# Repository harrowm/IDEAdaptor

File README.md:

# IDEAdaptor
A simple passive 40 to 44 pin ide adaptor board

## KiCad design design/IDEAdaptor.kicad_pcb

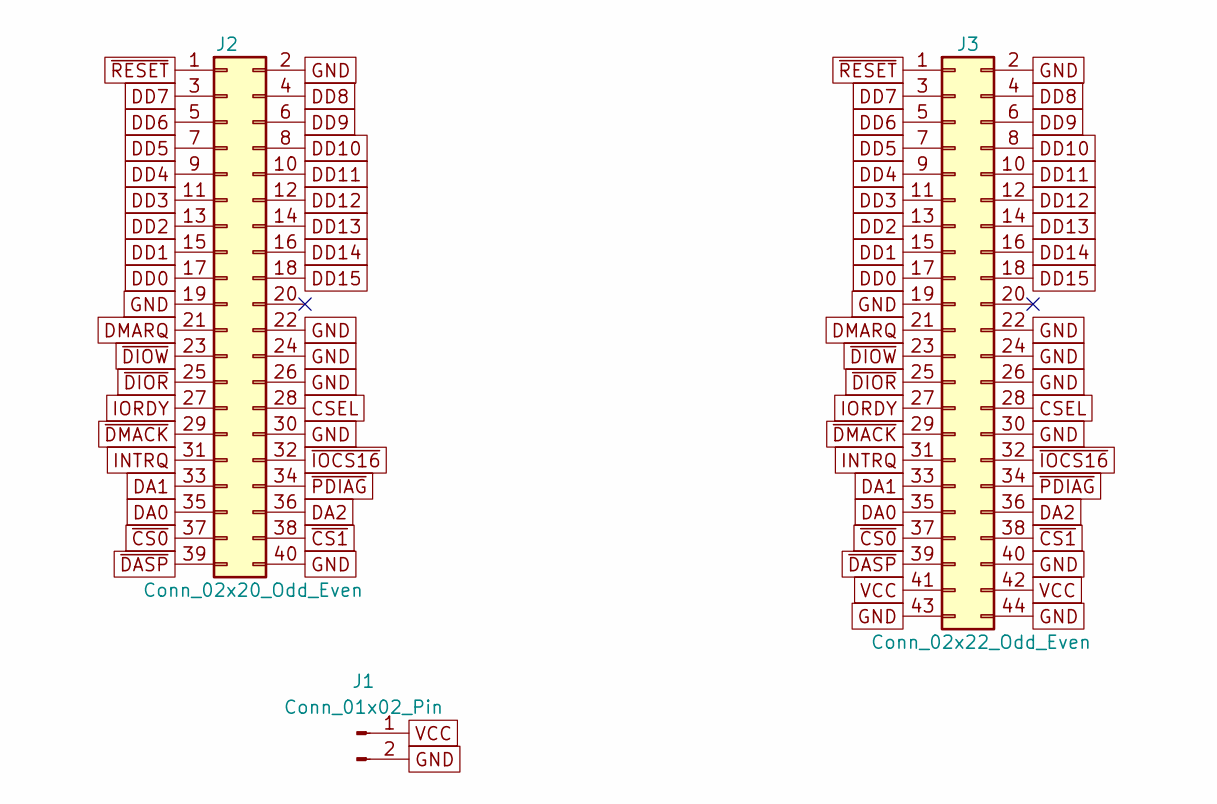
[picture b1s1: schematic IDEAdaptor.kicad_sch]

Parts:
J1: Conn_01x02_Pin; PinHeader_1x02_P2.54mm_Vertical
J2: Conn_02x20_Odd_Even; PinHeader_2x20_P2.54mm_Vertical
J3: Conn_02x22_Odd_Even; PinHeader_2x22_P2.00mm_Vertical

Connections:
CSEL: J2.28, J3.28
DA0: J2.35, J3.35
DA1: J2.33, J3.33
DA2: J2.36, J3.36
DD0: J2.17, J3.17
DD1: J2.15, J3.15
DD2: J2.13, J3.13
DD3: J2.11, J3.11
DD4: J2.9, J3.9
DD5: J2.7, J3.7
DD6: J2.5, J3.5
DD7: J2.3, J3.3
DD8: J2.4, J3.4
DD9: J2.6, J3.6
DD10: J2.8, J3.8
DD11: J2.10, J3.10
DD12: J2.12, J3.12
DD13: J2.14, J3.14
DD14: J2.16, J3.16
DD15: J2.18, J3.18
DMARQ: J2.21, J3.21
GND: J1.2, J2.2, J2.19, J2.22, J2.24, J2.26, J2.30, J2.40, J3.2, J3.19, J3.22, J3.24, J3.26, J3.30, J3.40, J3.43, J3.44
INTRQ: J2.31, J3.31
IORDY: J2.27, J3.27
VCC: J1.1, J3.41, J3.42
~CS0: J2.37, J3.37
~CS1: J2.38, J3.38
~DASP: J2.39, J3.39
~DIOR: J2.25, J3.25
~DIOW: J2.23, J3.23
~DMACK: J2.29, J3.29
~IOCS16: J2.32, J3.32
~PDIAG: J2.34, J3.34
~RESET: J2.1, J3.1

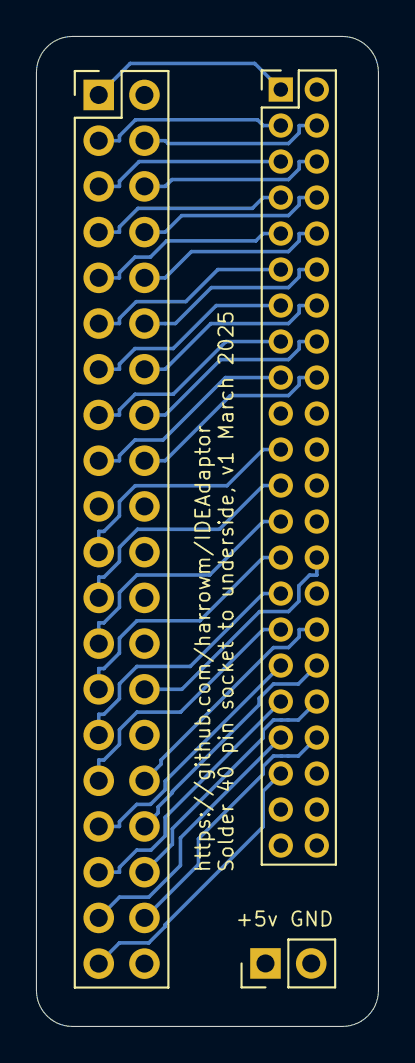
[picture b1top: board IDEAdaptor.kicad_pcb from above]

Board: 4 copper layers, 19.0 x 55.0 mm, 3 parts (0 on the bottom side), 34 nets.

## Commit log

2025-03-03 First version
